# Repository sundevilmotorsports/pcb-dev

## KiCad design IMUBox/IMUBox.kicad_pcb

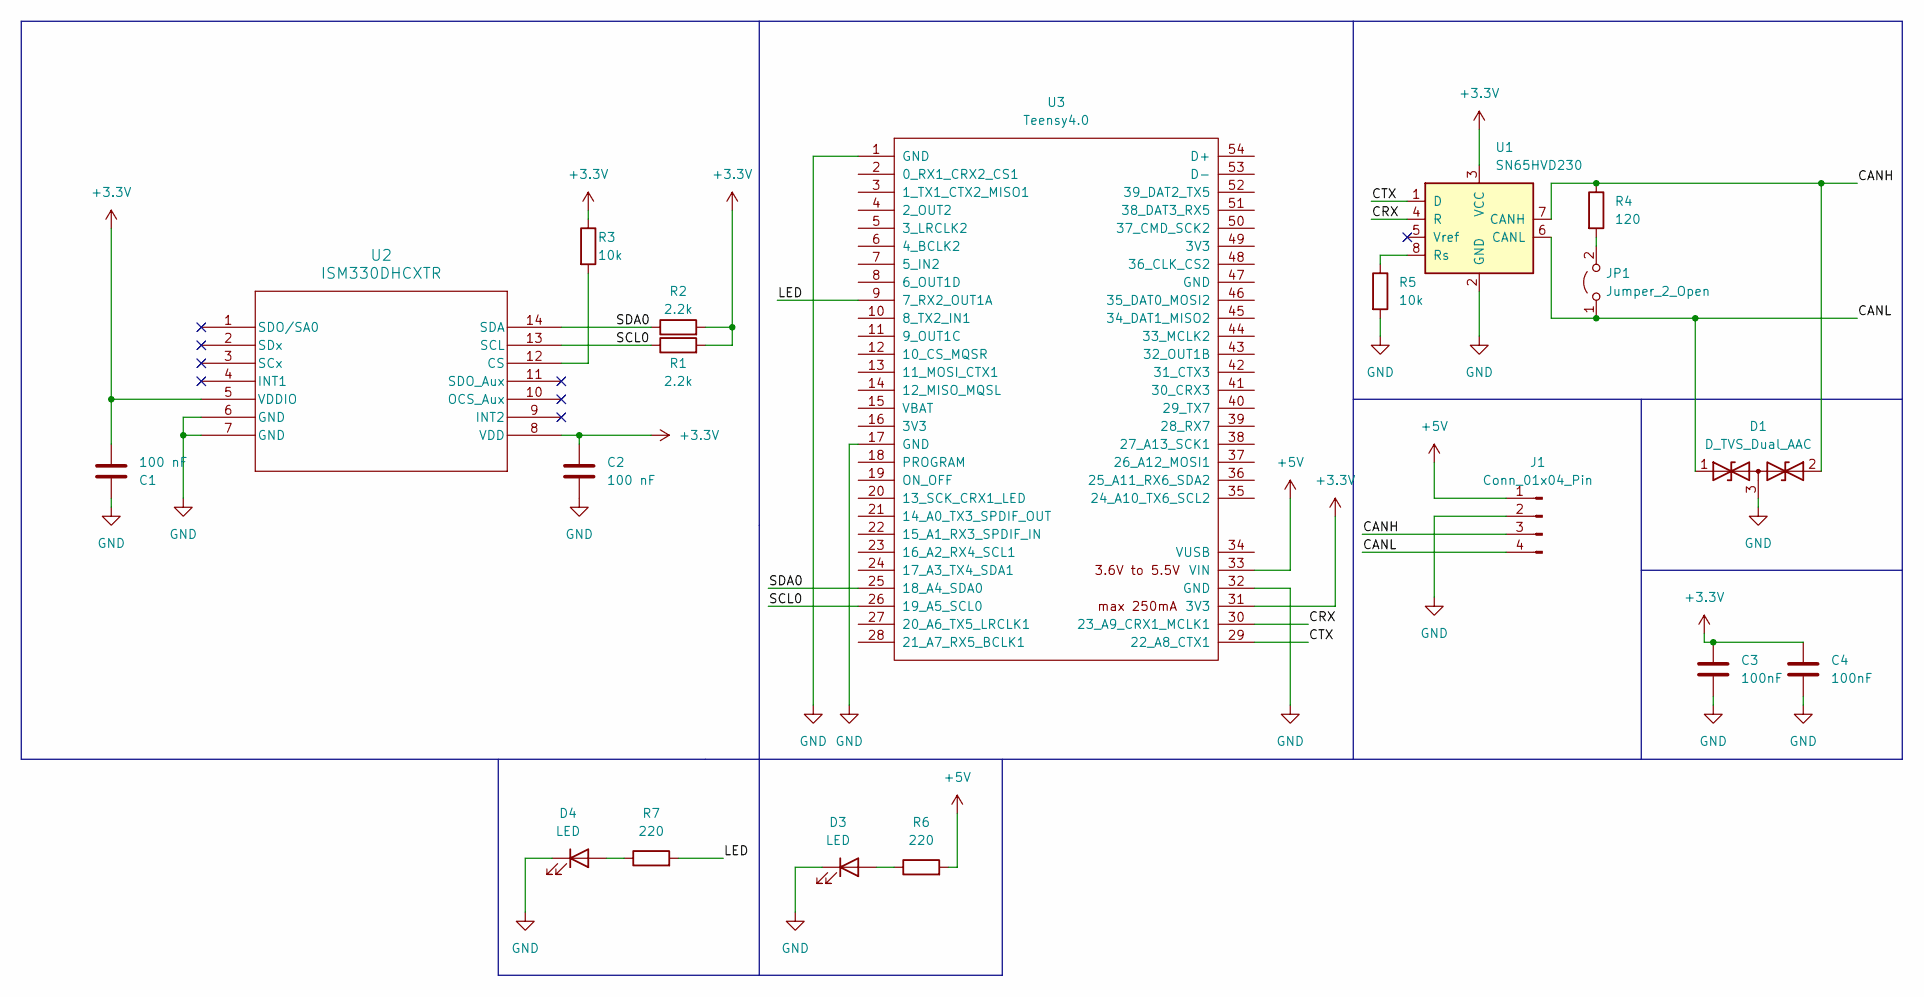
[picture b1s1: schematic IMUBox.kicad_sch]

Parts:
C1, C2: 100 nF; C_0402_1005Metric
C3, C4: 100nF; C_0402_1005Metric
D1: D_TVS_Dual_AAC; SOT-323_SC-70
D3, D4: LED; LED_1206_3216Metric
J1: Conn_01x04_Pin; JST_XA_B04B-XASK-1_1x04_P2.50mm_Vertical
JP1: Jumper_2_Open; PinHeader_1x02_P2.54mm_Vertical
R1, R2: 2.2k; R_0603_1608Metric
R3, R5: 10k; R_0805_2012Metric
R4: 120; R_0402_1005Metric
R6, R7: 220; R_0805_2012Metric
U1: SN65HVD230; SOIC-8_3.9x4.9mm_P1.27mm
U2: ISM330DHCXTR; LGA-14L
U3: Teensy4.0; Teensy40

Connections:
+3.3V: C1.2, C2.1, C3.1, C4.1, R1.2, R2.2, R3.1, U1.3 (VCC), U2.5 (VDDIO), U2.8 (VDD), U3.31 (3V3)
+5V: J1.1, R6.2, U3.33 (VIN)
/CANH: D1.2 (A2), J1.3, R4.1, U1.7 (CANH)
/CANL: D1.1 (A1), J1.4, JP1.1 (A), U1.6 (CANL)
/CRX: U1.4 (R), U3.30 (23_A9_CRX1_MCLK1)
/CTX: U1.1 (D), U3.29 (22_A8_CTX1)
/LED: R7.2, U3.9 (7_RX2_OUT1A)
/SCL0: R1.1, U2.13 (SCL), U3.26 (19_A5_SCL0)
/SDA0: R2.1, U2.14 (SDA), U3.25 (18_A4_SDA0)
GND: C1.1, C2.2, C3.2, C4.2, D1.3 (common), D3.1 (K), D4.1 (K), J1.2, R5.2, U1.2 (GND), U2.6 (GND), U2.7 (GND), U3.1 (GND), U3.17 (GND), U3.32 (GND)
unnamed: D3.2 (A), R6.1
unnamed: D4.2 (A), R7.1
unnamed: JP1.2 (B), R4.2
unnamed: R5.1, U1.8 (Rs)
unnamed: R3.2, U2.12 (CS)

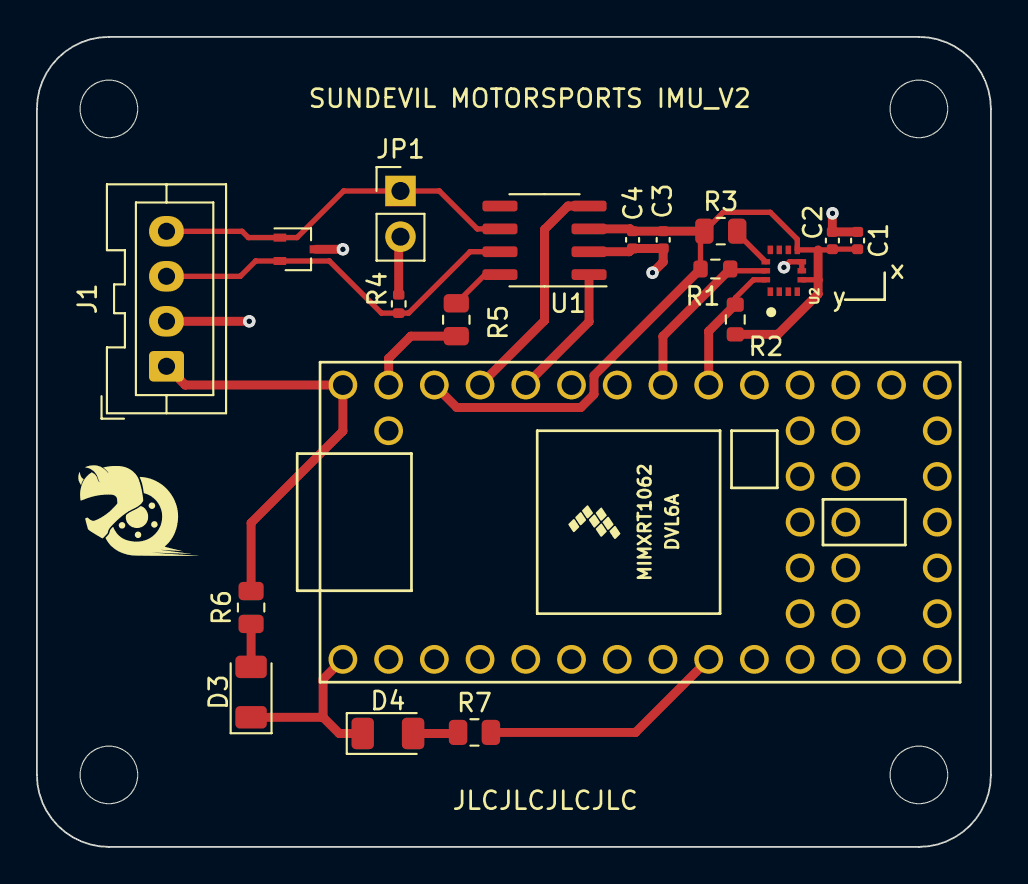
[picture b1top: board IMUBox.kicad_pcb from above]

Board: 2 copper layers, 53.0 x 45.0 mm, 19 parts (0 on the bottom side), 15 nets.

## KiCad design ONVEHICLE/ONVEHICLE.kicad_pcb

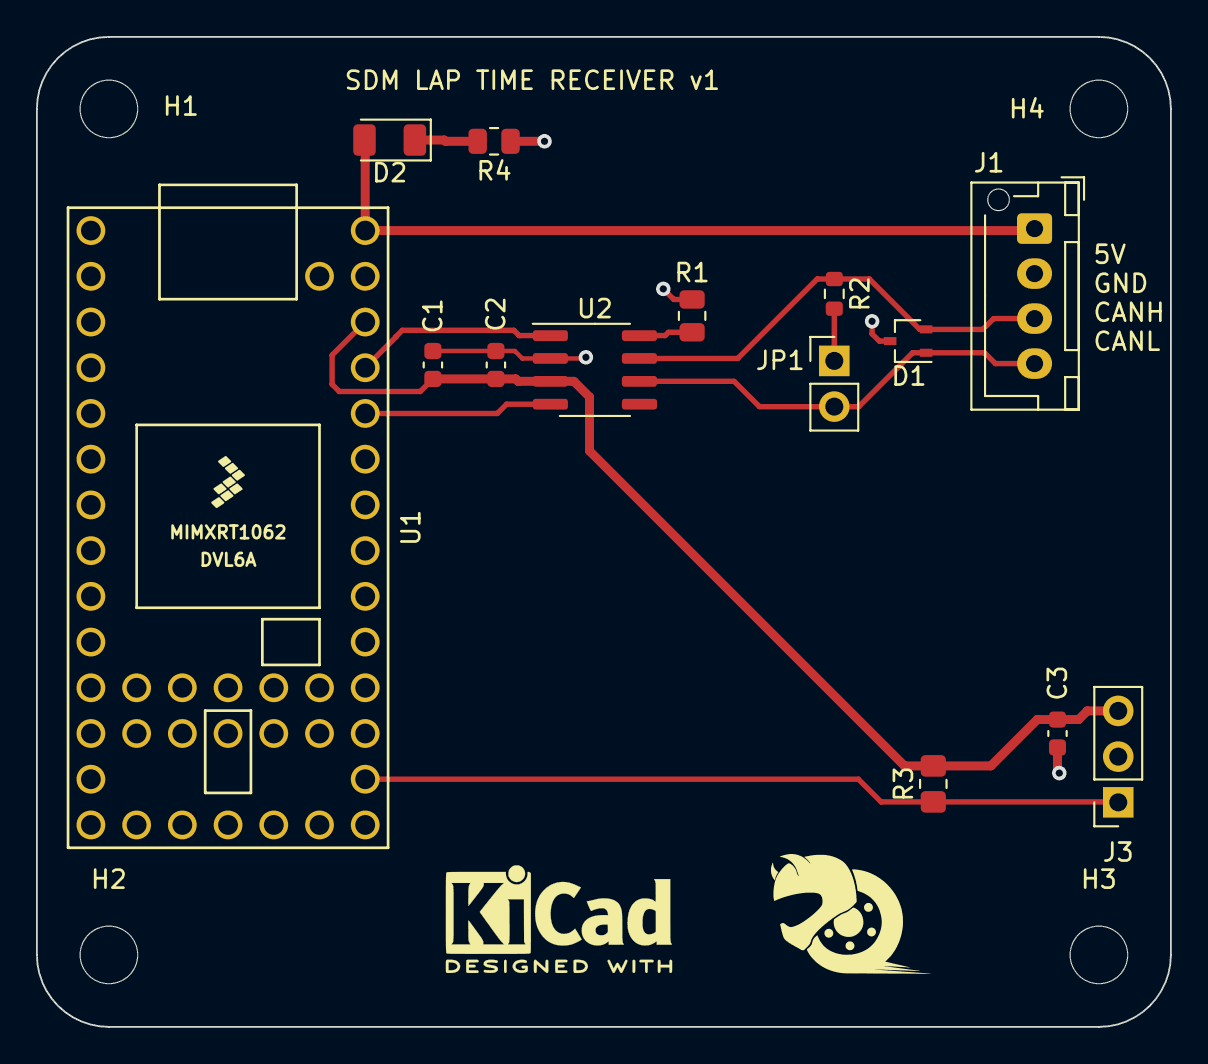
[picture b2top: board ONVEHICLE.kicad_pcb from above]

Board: 2 copper layers, 63.0 x 55.0 mm, 18 parts (0 on the bottom side), 11 nets.

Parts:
C1, C2, C3: 100nF; C_0603_1608Metric
D1: D_TVS_Dual_AAC; SOT-323_SC-70
D2: RED; LED_1206_3216Metric
H1, H2, H3, H4: MountingHole; MountingHole_3.2mm_M3
J1: Conn_01x04_Pin; JST_XH_B4B-XH-AM_1x04_P2.50mm_Vertical
J3: IR Sensor; PinSocket_1x03_P2.54mm_Vertical
JP1: Bus_Termination; PinHeader_1x02_P2.54mm_Vertical
R1: 10k; R_0805_2012Metric
R2: 120; R_0603_1608Metric
R3: 10k; R_0805_2012Metric_Pad1.20x1.40mm_HandSolder
R4: 160; R_0805_2012Metric
U1: Teensy4.0; Teensy40
U2: SN65HVD230; SOIC-8_3.9x4.9mm_P1.27mm

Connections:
+3.3V: C1.1, C2.1, C3.2, J3.3, R3.2, U1.31 (3V3), U2.3 (VCC)
+5V: D2.2 (A), J1.1, U1.33 (VIN)
/CANH: D1.2 (A2), J1.3, R2.1, U2.7 (CANH)
/CANL: D1.1 (A1), J1.4, JP1.2 (B), U2.6 (CANL)
/CRX: U1.30 (23_A9_CRX1_MCLK1), U2.1 (D)
/CTX: U1.29 (22_A8_CTX1), U2.4 (R)
/IRout: J3.1, R3.1, U1.21 (14_A0_TX3_SPDIF_OUT)
GND: C1.2, C2.2, C3.1, D1.3 (common), J1.2, J3.2, R1.2, R4.1, U1.1 (GND), U1.17 (GND), U1.32 (GND), U2.2 (GND)
unnamed: D2.1 (K), R4.2
unnamed: JP1.1 (A), R2.2
unnamed: R1.1, U2.8 (Rs)

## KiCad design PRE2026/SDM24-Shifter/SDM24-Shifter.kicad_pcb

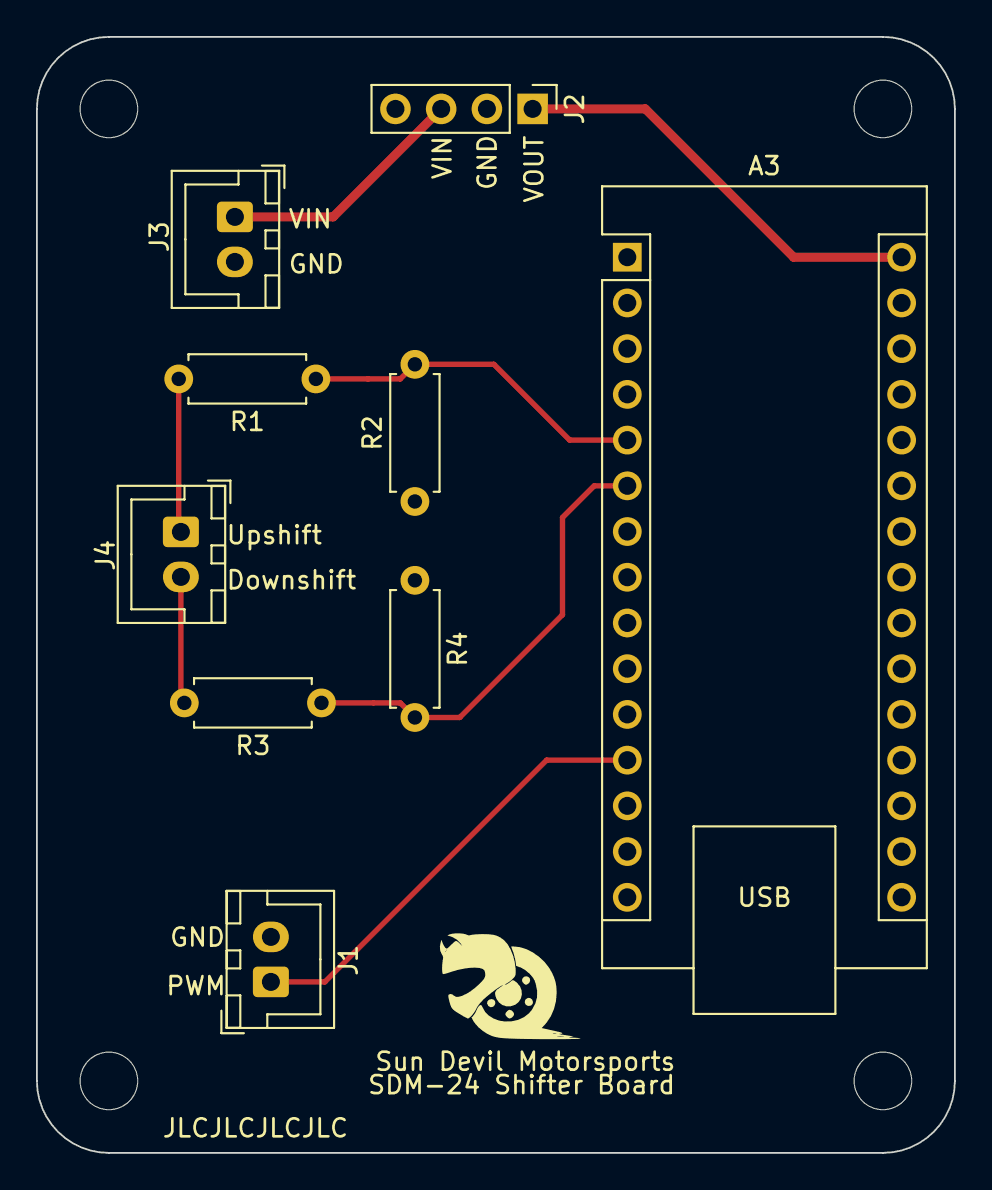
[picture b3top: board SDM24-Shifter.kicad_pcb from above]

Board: 2 copper layers, 51.0 x 62.0 mm, 13 parts (0 on the bottom side), 9 nets.

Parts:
A3: Arduino_Nano_v3.x; Arduino_Nano
H1, H2, H3, H4: MountingHole; MountingHole_3.2mm_M3
J1: PWM; JST_XH_B2B-XH-A_1x02_P2.50mm_Vertical
J2: Conn_01x04_Pin; PinHeader_1x04_P2.54mm_Vertical
J3: Power Input; JST_XH_B2B-XH-A_1x02_P2.50mm_Vertical
J4: Up/Down Shift; JST_XH_B2B-XH-A_1x02_P2.50mm_Vertical
R1, R3: 10k; R_Axial_DIN0207_L6.3mm_D2.5mm_P7.62mm_Horizontal
R2, R4: 5k; R_Axial_DIN0207_L6.3mm_D2.5mm_P7.62mm_Horizontal

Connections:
/VIN: J2.3, J3.1
/VOUT: A3.30 (VIN), J2.1
GND: A3.4 (GND), A3.29 (GND), J1.2
GND1: J2.2, J3.2, R2.1, R4.1
unnamed: A3.5 (D2), R1.1, R2.2
unnamed: A3.6 (D3), R3.1, R4.2
unnamed: A3.12 (D9), J1.1
unnamed: J4.1, R1.2
unnamed: J4.2, R3.2

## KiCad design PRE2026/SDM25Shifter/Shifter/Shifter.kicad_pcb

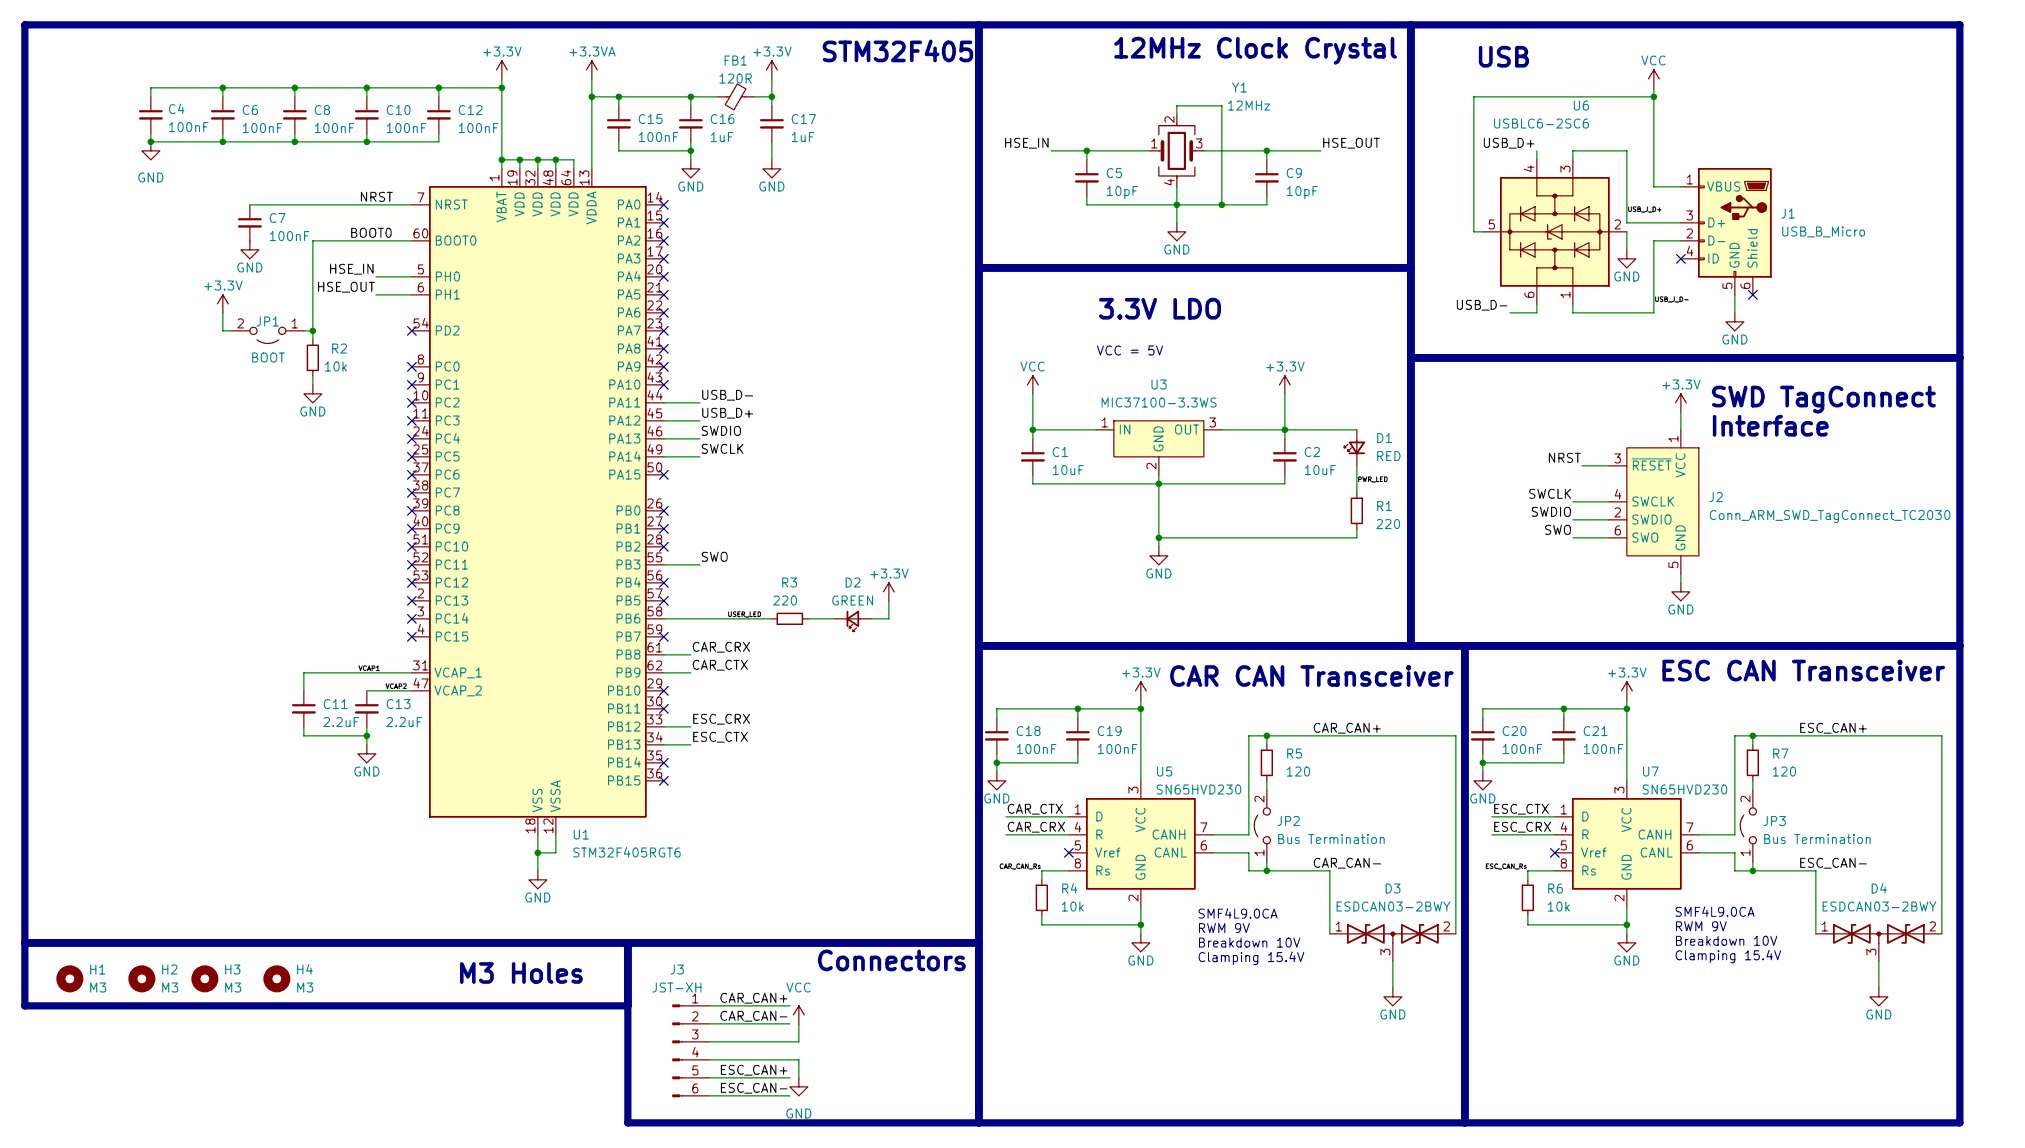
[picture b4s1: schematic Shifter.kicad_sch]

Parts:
C1, C2: 10uF; C_0603_1608Metric
C4, C6, C7, C8, C10, C12, C15, C18, C19, C20, C21: 100nF; C_0603_1608Metric
C5, C9: 10pF; C_0603_1608Metric
C11, C13: 2.2uF; C_0603_1608Metric
C16, C17: 1uF; C_0603_1608Metric
D1: RED; LED_0805_2012Metric
D2: GREEN; LED_0805_2012Metric
D3, D4: ESDCAN03-2BWY; SOT65P210X110-3N; Mouser Part Number 511-ESDCAN03-2BWY
FB1: 120R; L_0603_1608Metric
H1, H2, H3, H4: M3; MountingHole_3.2mm_M3
J1: USB_B_Micro; USB_Micro-B_Molex-105017-0001
J2: Conn_ARM_SWD_TagConnect_TC2030; Tag-Connect_TC2030-IDC-NL_2x03_P1.27mm_Vertical
J3: JST-XH; JST_XH_B6B-XH-A_1x06_P2.50mm_Vertical
JP1: BOOT; PinHeader_1x02_P2.54mm_Vertical
JP2, JP3: Bus Termination; PinHeader_1x02_P2.54mm_Vertical
R1, R3: 220; R_0603_1608Metric
R2, R4, R6: 10k; R_0603_1608Metric
R5, R7: 120; R_0603_1608Metric
U1: STM32F405RGT6; LQFP-64_10x10mm_P0.5mm
U3: MIC37100-3.3WS; SOT-223-3_TabPin2
U5, U7: SN65HVD230; SOIC-8_3.9x4.9mm_P1.27mm
U6: USBLC6-2SC6; SOT-23-6
Y1: 12MHz; Crystal_SMD_2520-4Pin_2.5x2.0mm

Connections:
+3.3V: C2.1, C4.1, C6.1, C8.1, C10.1, C12.1, C17.1, C18.1, C19.1, C20.1, C21.1, D1.2 (A), D2.2 (A), FB1.2, J2.1 (VCC), JP1.2 (B), U1.1 (VBAT), U1.19 (VDD), U1.32 (VDD), U1.48 (VDD), U1.64 (VDD), U3.3 (OUT), U5.3 (VCC), U7.3 (VCC)
+3.3VA: C15.1, C16.1, FB1.1, U1.13 (VDDA)
/BOOT0: JP1.1 (A), R2.2, U1.60 (BOOT0)
/CAR_CAN+: D3.2, J3.1, R5.1, U5.7 (CANH)
/CAR_CAN-: D3.1, J3.2, JP2.1 (A), U5.6 (CANL)
/CAR_CAN_Rs: R4.1, U5.8 (Rs)
/CAR_CRX: U1.61 (PB8), U5.4 (R)
/CAR_CTX: U1.62 (PB9), U5.1 (D)
/ESC_CAN+: D4.2, J3.5, R7.1, U7.7 (CANH)
/ESC_CAN-: D4.1, J3.6, JP3.1 (A), U7.6 (CANL)
/ESC_CAN_Rs: R6.1, U7.8 (Rs)
/ESC_CRX: U1.33 (PB12), U7.4 (R)
/ESC_CTX: U1.34 (PB13), U7.1 (D)
/HSE_IN: C5.1, U1.5 (PH0), Y1.1
/HSE_OUT: C9.1, U1.6 (PH1), Y1.3
/NRST: C7.1, J2.3 (~RESET), U1.7 (NRST)
/PWR_LED: D1.1 (K), R1.1
/SWCLK: J2.4 (SWCLK), U1.49 (PA14)
/SWDIO: J2.2 (SWDIO), U1.46 (PA13)
/SWO: J2.6 (SWO), U1.55 (PB3)
/USB_D+: U1.45 (PA12), U6.4 (I/O2)
/USB_D-: U1.44 (PA11), U6.6 (I/O1)
/USB_J_D+: J1.3 (D+), U6.3 (I/O2)
/USB_J_D-: J1.2 (D-), U6.1 (I/O1)
/USER_LED: R3.2, U1.58 (PB6)
/VCAP1: C11.1, U1.31 (VCAP_1)
/VCAP2: C13.1, U1.47 (VCAP_2)
GND: C1.2, C2.2, C4.2, C5.2, C6.2, C7.2, C8.2, C9.2, C10.2, C11.2, C12.2, C13.2, C15.2, C16.2, C17.2, C18.2, C19.2, C20.2, C21.2, D3.3, D4.3, J1.5 (GND), J2.5 (GND), J3.4, R1.2, R2.1, R4.2, R6.2, U1.12 (VSSA), U1.18 (VSS), U1.63 (VSS), U3.2 (GND), U5.2 (GND), U6.2 (GND), U7.2 (GND), Y1.2, Y1.4
unnamed: D2.1 (K), R3.1
unnamed: JP2.2 (B), R5.2
unnamed: JP3.2 (B), R7.2
VCC: C1.1, J1.1 (VBUS), J3.3, U3.1 (IN), U6.5 (VBUS)

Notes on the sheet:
USB
3.3V LDO
M3 Holes
CAR CAN Transceiver
SMF4L9.0CA RWM 9V Breakdown 10V Clamping 15.4V
Connectors
SWD TagConnect Interface
12MHz Clock Crystal
VCC = 5V
ESC CAN Transceiver
STM32F405

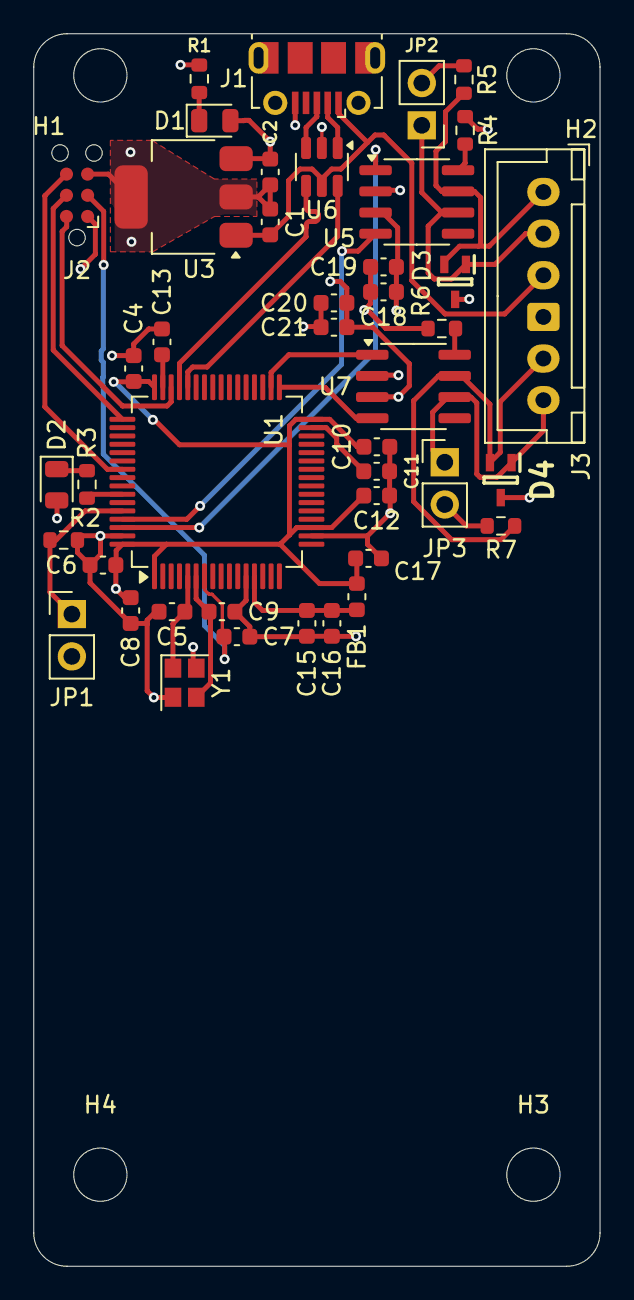
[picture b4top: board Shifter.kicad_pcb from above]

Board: 4 copper layers, 34.0 x 74.0 mm, 47 parts (0 on the bottom side), 32 nets.

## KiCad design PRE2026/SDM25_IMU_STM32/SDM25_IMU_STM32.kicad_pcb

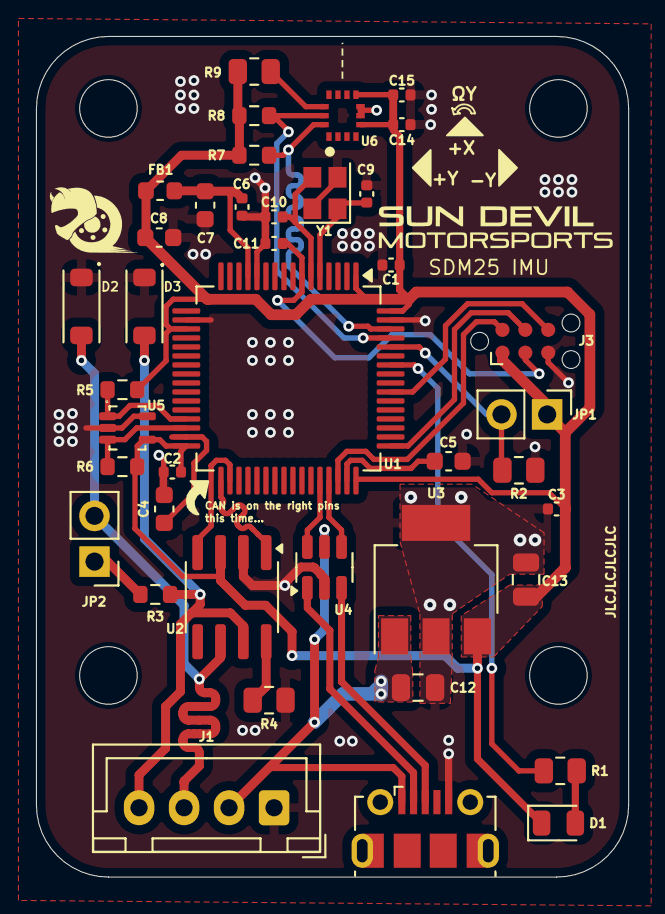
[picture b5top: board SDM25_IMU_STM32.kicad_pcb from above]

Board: 4 copper layers, 32.9 x 46.7 mm, 44 parts (0 on the bottom side), 30 nets.

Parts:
C1, C2, C3, C6, C11: 100nF; C_0402_1005Metric
C4, C5: 2.2uF; C_0603_1608Metric
C7, C8: 1uF; C_0603_1608Metric
C9, C10: 10pF; C_0402_1005Metric
C12, C13: 10uF; C_0805_2012Metric
C14, C15: 100 nF; C_0402_1005Metric
D1: GREEN; LED_0805_2012Metric
D2, D3: TVS; SOD-123FL
FB1: 120R; L_0603_1608Metric
H1, H2, H3, H4: M3; MountingHole_3.2mm_M3
J1: JST-XH; JST_XH_B4B-XH-A_1x04_P2.50mm_Vertical
J2: USB_B_Micro; USB_Micro-B_Molex-105017-0001
J3: Conn_ARM_SWD_TagConnect_TC2030; Tag-Connect_TC2030-IDC-NL_2x03_P1.27mm_Vertical
JP1: BOOT; PinHeader_1x02_P2.54mm_Vertical
JP2: Bus Termination; PinHeader_1x02_P2.54mm_Vertical
R1: 220; R_0805_2012Metric
R2, R4, R9: 10k; R_0805_2012Metric
R3: 120; R_0603_1608Metric
R5, R6: 2.7k; R_0603_1608Metric
R7, R8: 2.2k; R_0603_1608Metric
U1: STM32F405RGT6; LQFP-64_10x10mm_P0.5mm
U2: SN65HVD230; SOIC-8_3.9x4.9mm_P1.27mm
U3: MIC37100-3.3WS; SOT-223-3_TabPin2
U4: USBLC6-2SC6; SOT-23-6
U5: 24LC01BT-E/LT; SC-70-5
U6: ISM330DHCXTR; LGA-14L
Y1: 12MHz; Crystal_SMD_2520-4Pin_2.5x2.0mm

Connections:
+3.3V: C1.2, C2.2, C3.2, C8.2, C13.1, C14.2, C15.1, D1.1 (K), FB1.2, J3.1 (VCC), JP1.1 (A), R5.2, R6.2, R7.2, R8.2, R9.1, U1.1 (VBAT), U1.19 (VDD), U1.32 (VDD), U1.48 (VDD), U1.64 (VDD), U2.3 (VCC), U3.3 (OUT), U5.4 (Vcc), U6.5 (VDDIO), U6.8 (VDD)
/BOOT0: JP1.2 (B), R2.2, U1.60 (BOOT0)
/CANH: D3.2 (A2), J1.4, R3.1, U2.7 (CANH)
/CANL: D2.2 (A2), J1.3, JP2.2 (B), U2.6 (CANL)
/CRX: U1.CRX (PB12), U2.1 (D)
/CS: R9.2, U6.12 (CS)
/CTX: U1.34 (PB13), U2.4 (R)
/D+: J2.3 (D+), U4.3 (I/O2)
/D-: J2.2 (D-), U4.1 (I/O1)
/HSE_IN: C9.1, U1.5 (PH0), Y1.1
/HSE_OUT: C10.1, U1.6 (PH1), Y1.3
/I2C2_SCL: R5.1, U1.29 (PB10), U5.1 (SCL)
/I2C2_SDA: R6.1, U1.30 (PB11), U5.3 (SDA)
/NRST: C11.2, J3.3 (~RESET), U1.7 (NRST)
/Rs: R4.1, U2.8 (Rs)
/SDA0: R7.1, U1.62 (PB9), U6.14 (SDA)
/SWCLK: J3.4 (SWCLK), U1.49 (PA14)
/SWDIO: J3.2 (SWDIO), U1.46 (PA13)
/SWO: J3.6 (SWO), U1.55 (PB3)
/USB_D+: U1.45 (PA12), U4.4 (I/O2)
/USB_D-: U1.44 (PA11), U4.6 (I/O1)
/USER_LED: R1.2, U1.58 (PB6)
/VCAP_1: C4.1, U1.31 (VCAP_1)
/VCAP_2: C5.2, U1.47 (VCAP_2)
GND: C1.1, C2.1, C3.1, C4.2, C5.1, C6.1, C7.1, C8.1, C9.2, C10.2, C11.1, C12.2, C13.2, C14.1, C15.2, D2.1 (A1), D3.1 (A1), J1.1, J2.5 (GND), J3.5 (GND), R2.1, R4.2, U1.12 (VSSA), U1.18 (VSS), U1.63 (VSS), U2.2 (GND), U3.2 (GND), U4.2 (GND), U5.2 (Vss), U5.5 (WP), U6.6 (GND), U6.7 (GND), Y1.2, Y1.4
unnamed: D1.2 (A), R1.1
unnamed: JP2.1 (A), R3.2
unnamed: C6.2, C7.2, FB1.1, U1.13 (VDDA)
SCL0: R8.1, U1.61 (PB8), U6.13 (SCL)
VCC: C12.1, J1.2, J2.1 (VBUS), U3.1 (IN), U4.5 (VBUS)

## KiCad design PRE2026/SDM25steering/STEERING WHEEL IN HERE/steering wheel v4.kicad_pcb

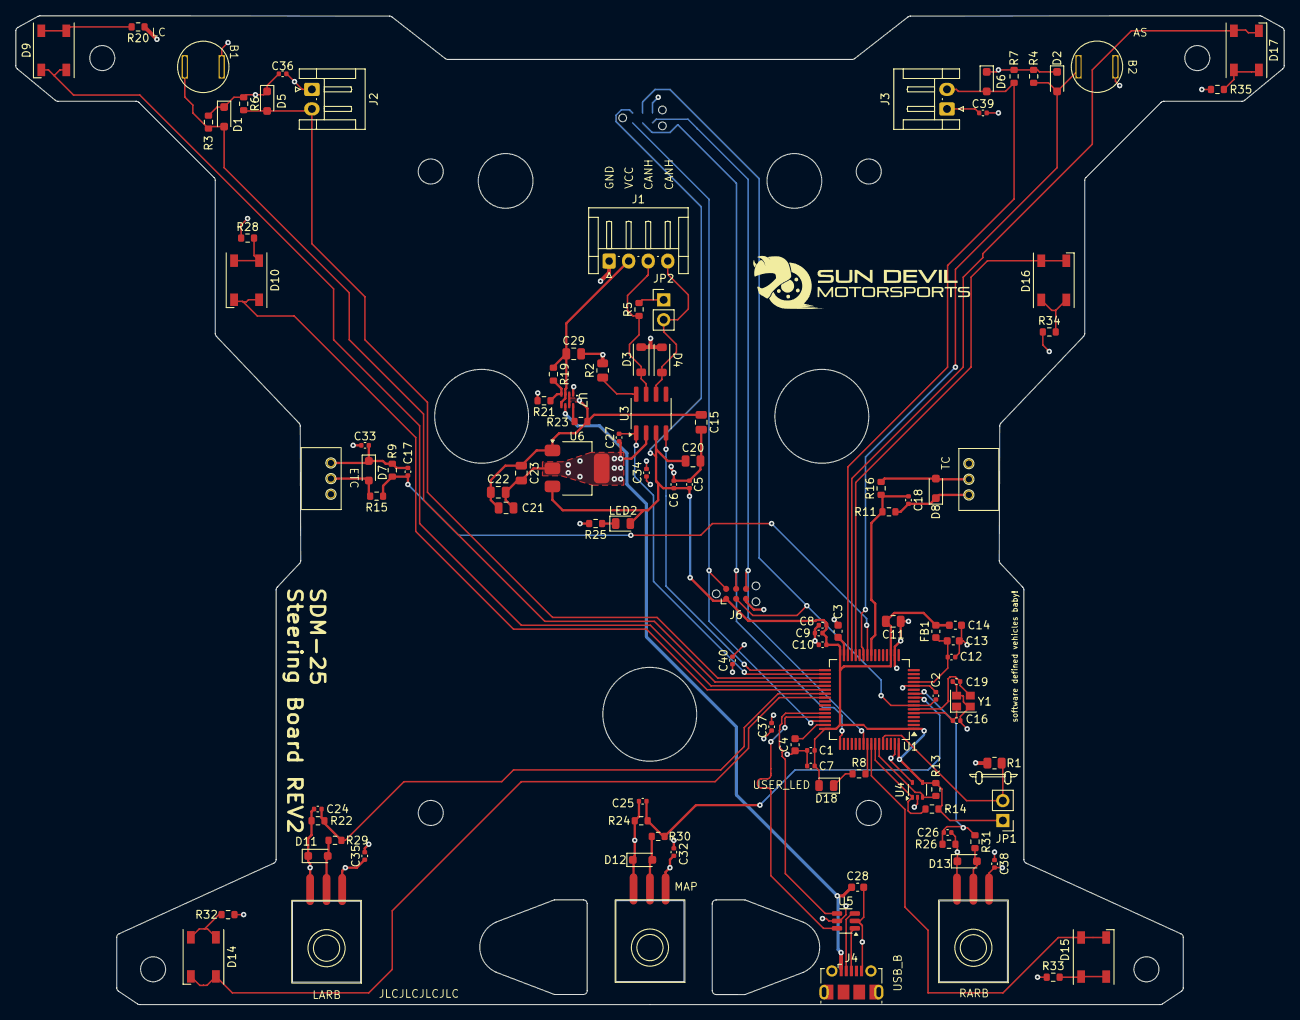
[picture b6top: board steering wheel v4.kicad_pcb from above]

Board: 4 copper layers, 162.2 x 126.4 mm, 118 parts (1 on the bottom side), 58 nets.

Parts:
B1, B2: Conn_01x02; 8631CQD2
C1, C2, C5, C6, C7, C8, C9, C10, C12, C27, C32, C33, C34, C35, C36, C37, C38, C39, C40: 100nF; C_0402_1005Metric
C3, C4: 2.2uF; C_0603_1608Metric
C11, C15, C20, C21, C22, C23, C29: 10uF; C_0805_2012Metric
C13, C14, C28: 1uF; C_0603_1608Metric
C16, C19: 10pF; C_0402_1005Metric
C17, C18, C24, C25, C26: 100n; C_0402_1005Metric
D1, D2, D5, D6, D7, D8, D11, D12, D13: TVS; D_SOD-323_HandSoldering
D3, D4: TVS; SOD-123FL
D9, D10, D14, D15, D16, D17: LTST-C235KGKRKT; LED_Cree-PLCC4_5x5mm_CW
D18: GREEN; LED_0805_2012Metric
FB1: 120R; L_0603_1608Metric
H1, H2, H3, H4, H5, H6, H7, H8: M3; MountingHole_3.2mm_M3
J1: Conn_01x04_Socket; JST_EH_S4B-EH_1x04_P2.50mm_Horizontal
J2, J3: Conn_01x02; JST_EH_S2B-EH_1x02_P2.50mm_Horizontal
J4: USB_B_Micro; USB_Micro-B_Molex-105017-0001
J5, J6: Conn_ARM_SWD_TagConnect_TC2030; Tag-Connect_TC2030-IDC-NL_2x03_P1.27mm_Vertical
JP1: BOOT; PinHeader_1x02_P2.54mm_Vertical
JP2: Bus Term.; PinHeader_1x02_P2.54mm_Vertical
LED2: RED; LED_0805_2012Metric
POT1, POT2, POT3, POT4, POT5: P081N-271F2CBR10K
R1, R2: 10k; R_0805_2012Metric
R3, R6, R7, R19, R21, R23: 10k; R_0603_1608Metric
R4, R8, R25: 220; R_0603_1608Metric
R5: 120; R_0603_1608Metric
R9, R11, R22, R24, R26: 2k; R_0603_1608Metric
R13, R14: 2.7k; R_0603_1608Metric
R15, R16, R29, R30, R31: 1k; R_0603_1608Metric
R20, R28, R32, R33, R34, R35: 330; R_0603_1608Metric
U1: STM32F405RGT6; LQFP-64_10x10mm_P0.5mm
U3: SN65HVD230; SOIC-8_3.9x4.9mm_P1.27mm
U4: 24LC01BT-E/LT; SOT-353_SC-70-5
U5: USBLC6-2SC6; SOT-23-6
U6: MIC37100-3.3WS; SOT-223-3_TabPin2
U7: TPS2116; SOT-5X3
Y1: 12MHz; Crystal_SMD_2520-4Pin_2.5x2.0mm

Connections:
+3.3V: C1.2, C5.2, C6.2, C7.2, C8.2, C9.2, C10.2, C11.2, C14.2, C20.1, D18.2 (A), FB1.2, J5.1 (VCC), J6.1 (VCC), JP1.1 (A), LED2.2 (A), R13.2, R14.2, U1.1 (VBAT), U1.19 (VDD), U1.32 (VDD), U1.48 (VDD), U1.64 (VDD), U3.3 (VCC), U4.4 (Vcc), U6.3 (OUT)
+5VD: C29.1, J1.2, R19.1, U7.3 (VIN1), U7.5 (MODE)
/AIN1: C24.1, R22.1, R29.1, U1.39 (PC8)
/AIN2: C25.1, R24.1, R30.1, U1.9 (PC1)
/AIN3: C26.1, R26.1, R31.1, U1.10 (PC2)
/AIN5: C18.1, R11.1, R16.1, U1.24 (PC4)
/AIN6: C17.1, R9.1, R15.1, U1.25 (PC5)
/BOOT0: JP1.2 (B), R1.2, U1.60 (BOOT0)
/BUTTON_AS: B2.2, D2.2 (A2), R4.2, U1.26 (PB0)
/BUTTON_LC: B1.2, D1.2 (A2), R3.2, U1.36 (PB15)
/CANH: D3.1 (A1), J1.3, R5.1, U3.7 (CANH)
/CANL: D4.2 (A2), J1.4, JP2.2 (B), U3.6 (CANL)
/CRX: U1.33 (PB12), U3.4 (R)
/CTX: C27.2, U1.34 (PB13), U3.1 (D)
/D+: J4.3 (D+), U5.1 (I/O1)
/D-: J4.2 (D-), U5.3 (I/O2)
/HSE_IN: C16.1, U1.5 (PH0), Y1.1
/HSE_OUT: C19.1, U1.6 (PH1), Y1.3
/I2C1_SCL: R14.1, U1.58 (PB6), U4.1 (SCL)
/I2C1_SDA: R13.1, U1.59 (PB7), U4.3 (SDA)
/LED1: D9.1 (K2), D9.4 (K1), U1.37 (PC6)
/LED2: D10.1 (K2), D10.4 (K1), U1.38 (PC7)
/LED3: D14.1 (K2), D14.4 (K1), U1.40 (PC9)
/LED4: D15.1 (K2), D15.4 (K1), U1.57 (PB5)
/LED5: D16.1 (K2), D16.4 (K1), U1.28 (PB2)
/LED6: D17.1 (K2), D17.4 (K1), U1.29 (PB10)
/NRST: C2.2, J5.3 (~RESET), J6.3 (~RESET), U1.7 (NRST)
/POT_ETC: D7.2 (A2), POT1.2 (VDD), R15.2
/POT_LARB: D11.2 (A2), POT3.2 (SIG), R29.2
/POT_MAP: D12.2 (A2), POT4.2 (SIG), R30.2
/POT_RARB: D13.2 (A2), POT5.2 (SIG), R31.2
/POT_TC: D8.2 (A2), POT2.2 (SIG), R16.2
/Rs: R2.1, U3.8 (Rs)
/SHIFT1: D5.2 (A2), J2.2, R6.2, U1.35 (PB14)
/SHIFT2: D6.2 (A2), J3.2, R7.2, U1.30 (PB11)
/SWCLK: J5.4 (SWCLK), J6.4 (SWCLK), U1.49 (PA14)
/SWDIO: J5.2 (SWDIO), J6.2 (SWDIO), U1.46 (PA13)
/SWO: J5.6 (SWO), J6.6 (SWO), U1.55 (PB3)
/USB_D+: U1.45 (PA12), U5.6 (I/O1)
/USB_D-: U1.44 (PA11), U5.4 (I/O2)
/USER_LED: R8.2, U1.56 (PB4)
/VCAP_1: C3.1, U1.31 (VCAP_1)
/VCAP_2: C4.2, U1.47 (VCAP_2)
GND: C1.1, C2.1, C3.2, C4.1, C5.1, C6.1, C7.1, C8.1, C9.1, C10.1, C11.1, C12.1, C13.1, C14.1, C15.2, C16.2, C17.2, C18.2, C19.2, C20.2, C21.2, C22.2, C23.2, C24.2, C25.2, C26.2, C27.1, C28.2, C29.2, C32.2, C33.2, C34.2, C35.2, C36.2, C37.2, C38.2, C39.2, C40.2, D1.1 (A1), D2.1 (A1), D3.2 (A2), D4.1 (A1), D5.1 (A1), D6.1 (A1), D7.1 (A1), D8.1 (A1), D11.1 (A1), D12.1 (A1), D13.1 (A1), J1.1, J4.5 (GND), J5.5 (GND), J6.5 (GND), POT1.3 (VDD), POT2.3 (GND), POT3.3 (GND), POT4.3 (GND), POT5.3 (GND), R1.1, R2.2, R3.1, R4.1, R6.1, R7.1, R9.2, R11.2, R21.2, R22.2, R24.2, R25.2, R26.2, U1.12 (VSSA), U1.18 (VSS), U1.63 (VSS), U3.2 (GND), U4.2 (Vss), U4.5 (WP), U5.2 (GND), U6.2 (GND), U7.1 (GND), Y1.2, Y1.4
unnamed: D9.2 (A2), D9.3 (A1), R20.2
unnamed: D10.2 (A2), D10.3 (A1), R28.2
unnamed: D14.2 (A2), D14.3 (A1), R32.2
unnamed: D15.2 (A2), D15.3 (A1), R33.2
unnamed: D16.2 (A2), D16.3 (A1), R34.2
unnamed: D17.2 (A2), D17.3 (A1), R35.2
unnamed: D18.1 (K), R8.1
unnamed: JP2.1 (A), R5.2
unnamed: LED2.1 (K), R25.1
unnamed: C12.2, C13.2, FB1.1, U1.13 (VDDA)
unnamed: R19.2, R21.1, U7.4 (PR1)
unnamed: R23.2, U7.8 (ST)
VBUS: C28.1, J4.1 (VBUS), U7.6 (VIN2)
VCC: B1.1, B2.1, C15.1, C21.1, C22.1, C23.1, C32.1, C33.1, C34.1, C35.1, C36.1, C37.1, C38.1, C39.1, C40.1, J2.1, J3.1, POT1.1 (VDD), POT2.1 (VDD), POT3.1 (VDD), POT4.1 (VDD), POT5.1 (VDD), R20.1, R23.1, R28.1, R32.1, R33.1, R34.1, R35.1, U5.5 (VBUS), U6.1 (IN), U7.2 (VOUT), U7.7 (VOUT)
